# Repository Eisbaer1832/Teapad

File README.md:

# 🫖 Teapad 🫖
Teapad is a KMK based 3 by 3 macropad in the shape of a teapod.

This project is based of the amazing [Hackclub Hackpad](https://hackpad.hackclub.com/submitting) template.

## CAD Model
The Case is held together by 6 M3 Bolts and nuts.
Printable Parts are located in the [production directory](https://github.com/Eisbaer1832/Teapad/tree/main/production).

## PCB
The PCB was created in KiCad, source Files are located in the [PCB directory](https://github.com/Eisbaer1832/Teapad/tree/main/PCB).

## Firmware
At the moment, the KMK firmware just calls Shortcuts I use for voice chatting or music and opens some programms via the os lib. 
Customizable QT Frontend to change these and implement LED Status codes is comming soon ™️.

## BOM
* 1x Seeed XIAO RP2040
* 2x Through-hole 1N4148 Diodes
* 9x Cherry MX Switches
* 9x DSA keycaps
* 6x M3x16mm screws
* 6x M3 nuts (self provided)
* 1x Case (1x Top, 1x Bottom)

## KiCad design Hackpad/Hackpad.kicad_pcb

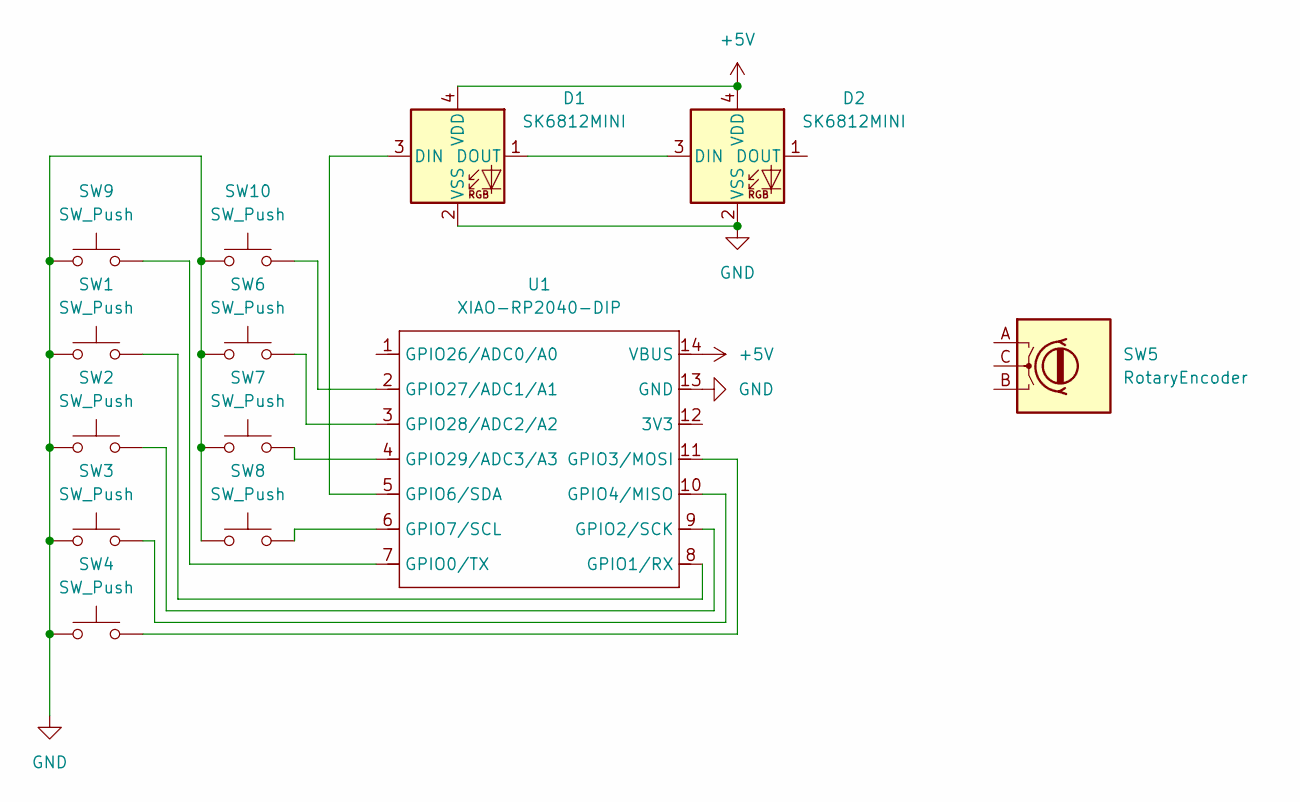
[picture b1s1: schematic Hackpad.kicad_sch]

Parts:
D1, D2: SK6812MINI; LED_SK6812MINI_PLCC4_3.5x3.5mm_P1.75mm
SW1, SW2, SW3, SW4, SW6, SW7, SW8, SW9, SW10: SW_Push; SW_Cherry_MX_1.00u_PCB
SW5: RotaryEncoder; RotaryEncoder_Alps_EC11E-Switch_Vertical_H20mm
U1: XIAO-RP2040-DIP

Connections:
+5V: D1.4 (VDD), D2.4 (VDD), U1.14 (VBUS)
GND: D1.2 (VSS), D2.2 (VSS), SW1.2, SW2.2, SW3.2, SW4.2, SW6.2, SW7.2, SW8.2, SW9.2, SW10.2, U1.13 (GND)
unnamed: D1.3 (DIN), U1.5 (GPIO6/SDA)
unnamed: D1.1 (DOUT), D2.3 (DIN)
unnamed: SW9.1, U1.7 (GPIO0/TX)
unnamed: SW1.1, U1.8 (GPIO1/RX)
unnamed: SW2.1, U1.9 (GPIO2/SCK)
unnamed: SW4.1, U1.11 (GPIO3/MOSI)
unnamed: SW3.1, U1.10 (GPIO4/MISO)
unnamed: SW8.1, U1.6 (GPIO7/SCL)
unnamed: SW10.1, U1.2 (GPIO27/ADC1/A1)
unnamed: SW6.1, U1.3 (GPIO28/ADC2/A2)
unnamed: SW7.1, U1.4 (GPIO29/ADC3/A3)

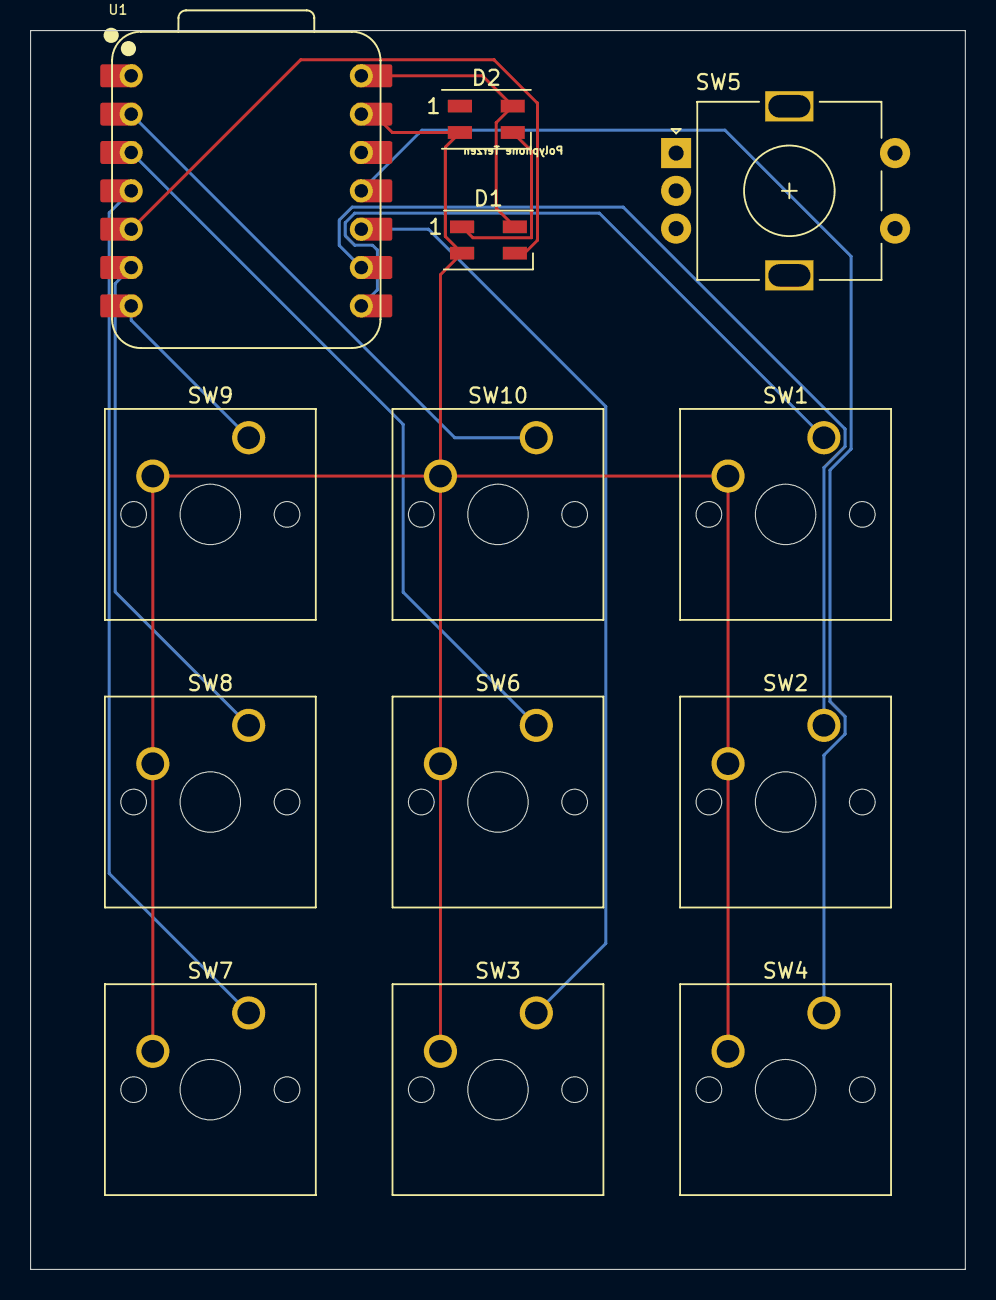
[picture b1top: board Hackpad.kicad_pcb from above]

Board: 2 copper layers, 61.9 x 82.1 mm, 13 parts (0 on the bottom side), 13 nets.

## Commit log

2025-06-05 blubsi
2025-06-16 updated pcb
2025-07-26 finished pcb
2025-07-27 finished production version
2025-07-27 removed submodules
2025-07-27 removed raw gerbers
2025-07-27 added assets for the readme
